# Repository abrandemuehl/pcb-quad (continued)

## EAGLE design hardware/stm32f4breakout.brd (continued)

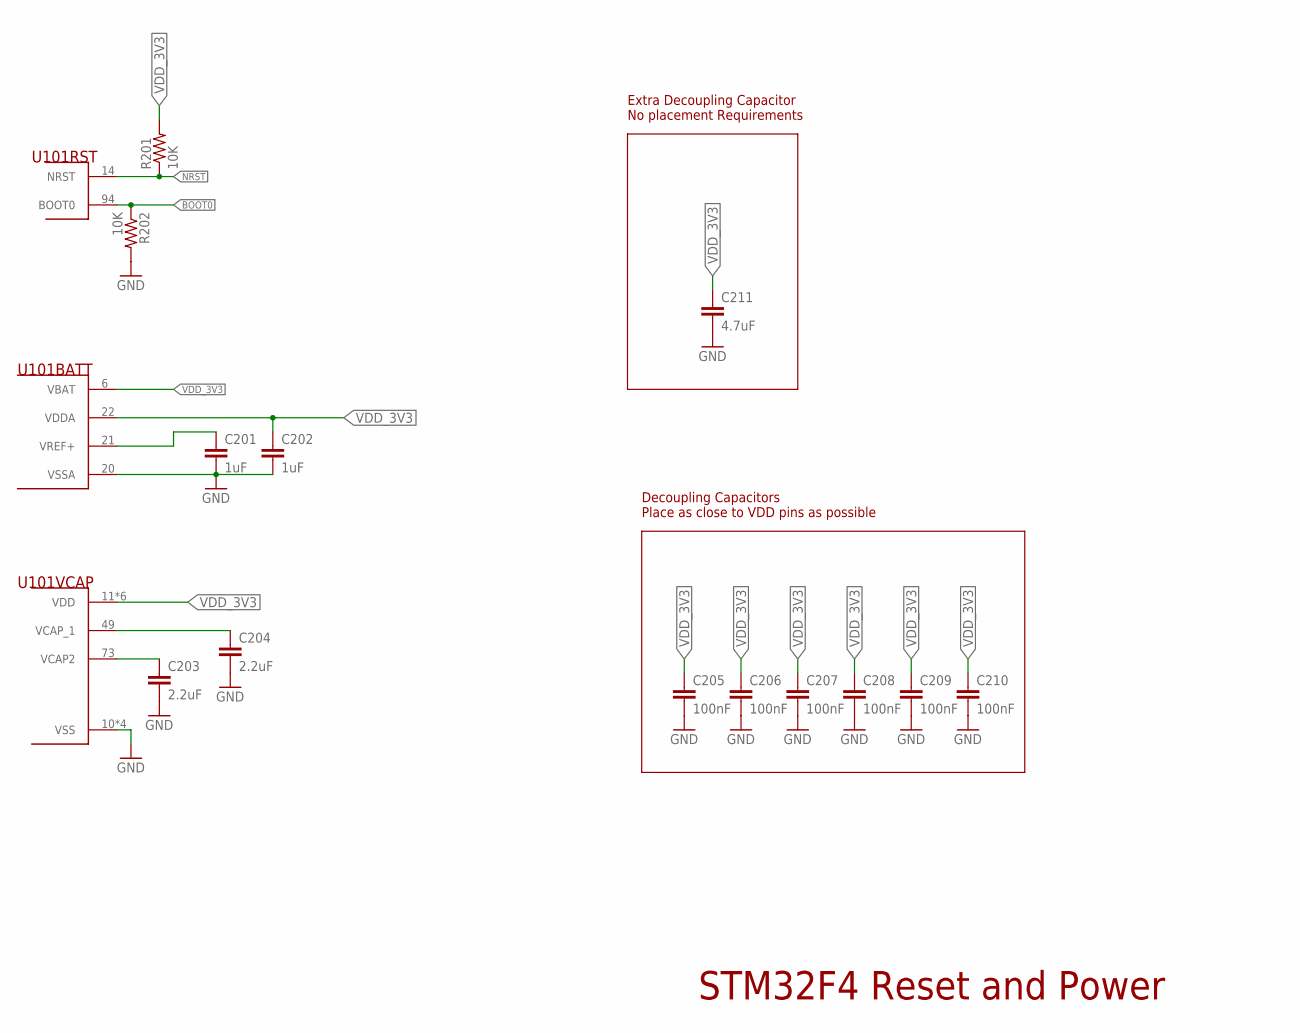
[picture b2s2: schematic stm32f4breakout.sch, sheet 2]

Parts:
C201, C202: 1uF; C0603
C203, C204: 2.2uF; C0603
C205, C206, C207, C208, C209, C210: 100nF; C0603
C211: 4.7uF; C0603
R201, R202: 10K; R0603
U101: STM32F427VGT6; LQFP-100

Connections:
BOOT0: R202.1, U101.94 (BOOT0); also elsewhere on the board
GND: C201.2, C202.2, C203.2, C204.2, C205.2, C206.2, C207.2, C208.2, C209.2, C210.2, C211.2, R202.2, U101.10 (VSS), U101.20 (VSSA), U101.27 (VSS), U101.74 (VSS), U101.99 (VSS); also elsewhere on the board
NRST: R201.1, U101.14 (NRST); also elsewhere on the board
VCAP2: C203.1, U101.73 (VCAP2)
VCAP_1: C204.1, U101.49 (VCAP_1)
VDD_3V3: C201.1, C202.1, C205.1, C206.1, C207.1, C208.1, C209.1, C210.1, C211.1, R201.2, U101.6 (VBAT), U101.11 (VDD), U101.19 (VDD), U101.21 (VREF+), U101.22 (VDDA), U101.28 (VDD), U101.50 (VDD), U101.75 (VDD), U101.100 (VDD); also elsewhere on the board

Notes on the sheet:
STM32F4 Reset and Power
Decoupling Capacitors Place as close to VDD pins as possible
Extra Decoupling Capacitor No placement Requirements

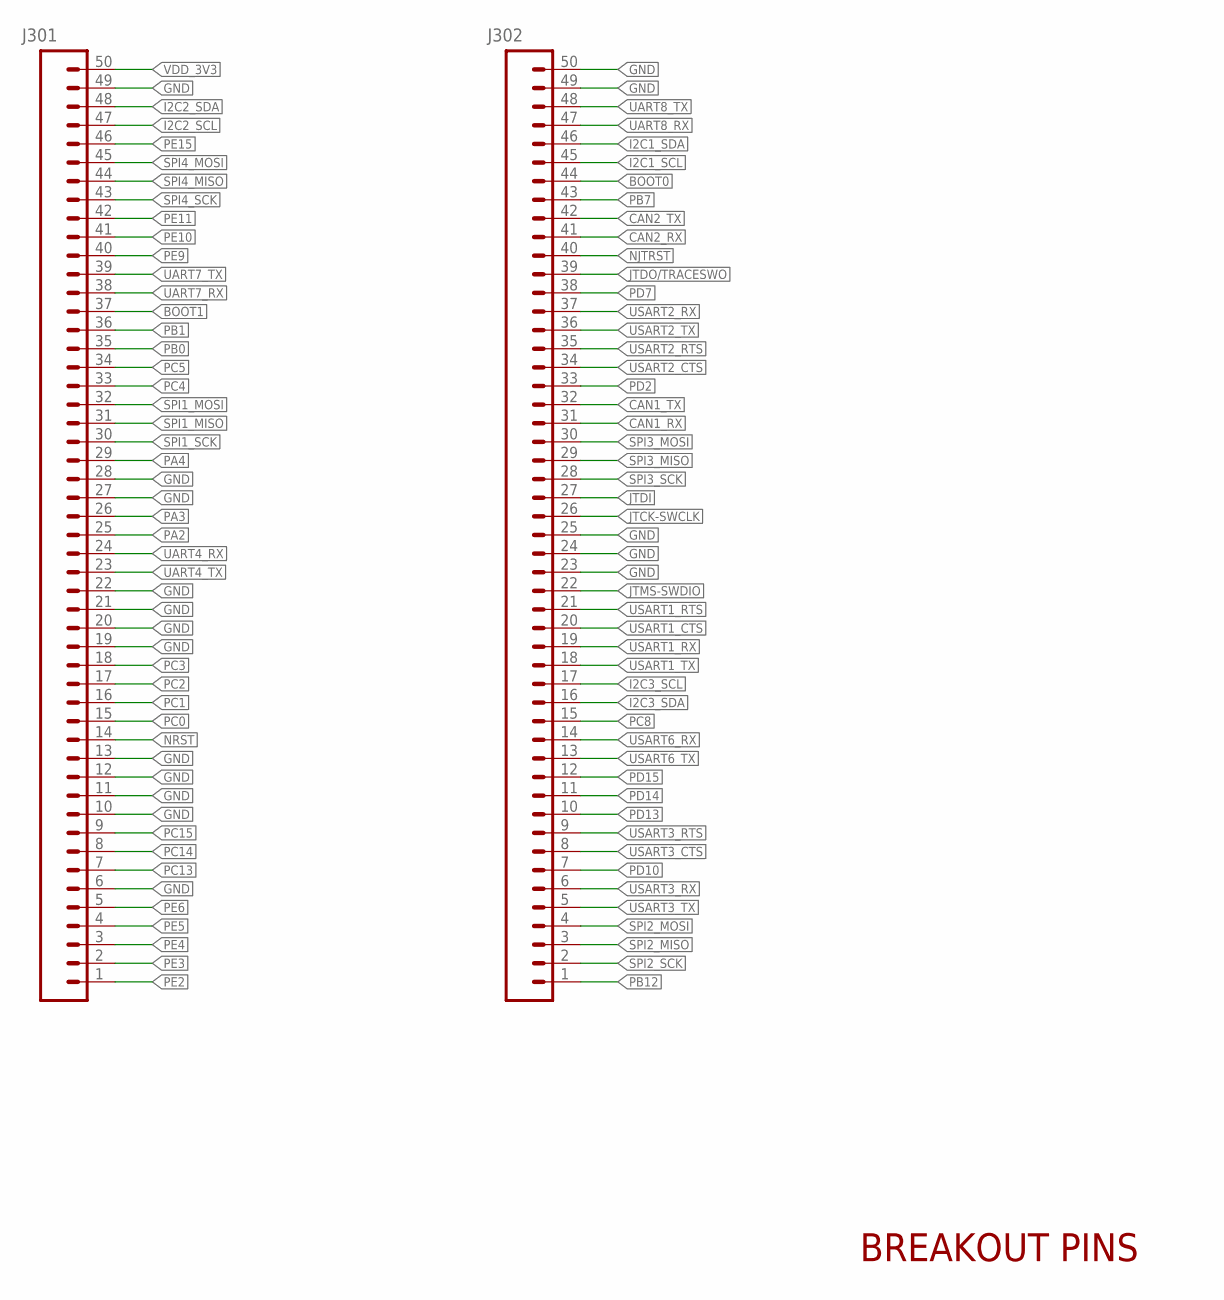
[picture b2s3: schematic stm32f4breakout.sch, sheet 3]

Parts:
J301, J302: PINHD-1X50; 1X50

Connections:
BOOT0: J302.44; also elsewhere on the board
BOOT1: J301.37; also elsewhere on the board
CAN1_RX: J302.31; also elsewhere on the board
CAN1_TX: J302.32; also elsewhere on the board
CAN2_RX: J302.41; also elsewhere on the board
CAN2_TX: J302.42; also elsewhere on the board
GND: J301.6, J301.10, J301.11, J301.12, J301.13, J301.19, J301.20, J301.21, J301.22, J301.27, J301.28, J301.49, J302.23, J302.24, J302.25, J302.49, J302.50; also elsewhere on the board
I2C1_SCL: J302.45; also elsewhere on the board
I2C1_SDA: J302.46; also elsewhere on the board
I2C2_SCL: J301.47; also elsewhere on the board
I2C2_SDA: J301.48; also elsewhere on the board
I2C3_SCL: J302.17; also elsewhere on the board
I2C3_SDA: J302.16; also elsewhere on the board
JTCK-SWCLK: J302.26; also elsewhere on the board
JTDI: J302.27; also elsewhere on the board
JTDO/TRACESWO: J302.39; also elsewhere on the board
JTMS-SWDIO: J302.22; also elsewhere on the board
NJTRST: J302.40; also elsewhere on the board
NRST: J301.14; also elsewhere on the board
PA2: J301.25; also elsewhere on the board
PA3: J301.26; also elsewhere on the board
PA4: J301.29; also elsewhere on the board
PB0: J301.35; also elsewhere on the board
PB1: J301.36; also elsewhere on the board
PB7: J302.43; also elsewhere on the board
PB12: J302.1; also elsewhere on the board
PC0: J301.15; also elsewhere on the board
PC1: J301.16; also elsewhere on the board
PC2: J301.17; also elsewhere on the board
PC3: J301.18; also elsewhere on the board
PC4: J301.33; also elsewhere on the board
PC5: J301.34; also elsewhere on the board
PC8: J302.15; also elsewhere on the board
PC13: J301.7; also elsewhere on the board
PC14: J301.8; also elsewhere on the board
PC15: J301.9; also elsewhere on the board
PD2: J302.33; also elsewhere on the board
PD7: J302.38; also elsewhere on the board
PD10: J302.7; also elsewhere on the board
PD13: J302.10; also elsewhere on the board
PD14: J302.11; also elsewhere on the board
PD15: J302.12; also elsewhere on the board
PE2: J301.1; also elsewhere on the board
PE3: J301.2; also elsewhere on the board
PE4: J301.3; also elsewhere on the board
PE5: J301.4; also elsewhere on the board
PE6: J301.5; also elsewhere on the board
PE9: J301.40; also elsewhere on the board
PE10: J301.41; also elsewhere on the board
PE11: J301.42; also elsewhere on the board
PE15: J301.46; also elsewhere on the board
SPI1_MISO: J301.31; also elsewhere on the board
SPI1_MOSI: J301.32; also elsewhere on the board
SPI1_SCK: J301.30; also elsewhere on the board
SPI2_MISO: J302.3; also elsewhere on the board
SPI2_MOSI: J302.4; also elsewhere on the board
SPI2_SCK: J302.2; also elsewhere on the board
SPI3_MISO: J302.29; also elsewhere on the board
SPI3_MOSI: J302.30; also elsewhere on the board
SPI3_SCK: J302.28; also elsewhere on the board
SPI4_MISO: J301.44; also elsewhere on the board
SPI4_MOSI: J301.45; also elsewhere on the board
SPI4_SCK: J301.43; also elsewhere on the board
UART4_RX: J301.24; also elsewhere on the board
UART4_TX: J301.23; also elsewhere on the board
UART7_RX: J301.38; also elsewhere on the board
UART7_TX: J301.39; also elsewhere on the board
UART8_RX: J302.47; also elsewhere on the board
UART8_TX: J302.48; also elsewhere on the board
USART1_CTS: J302.20; also elsewhere on the board
USART1_RTS: J302.21; also elsewhere on the board
USART1_RX: J302.19; also elsewhere on the board
USART1_TX: J302.18; also elsewhere on the board
USART2_CTS: J302.34; also elsewhere on the board
USART2_RTS: J302.35; also elsewhere on the board
USART2_RX: J302.37; also elsewhere on the board
USART2_TX: J302.36; also elsewhere on the board
USART3_CTS: J302.8; also elsewhere on the board
USART3_RTS: J302.9; also elsewhere on the board
USART3_RX: J302.6; also elsewhere on the board
USART3_TX: J302.5; also elsewhere on the board
USART6_RX: J302.14; also elsewhere on the board
USART6_TX: J302.13; also elsewhere on the board
VDD_3V3: J301.50; also elsewhere on the board

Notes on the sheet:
BREAKOUT PINS

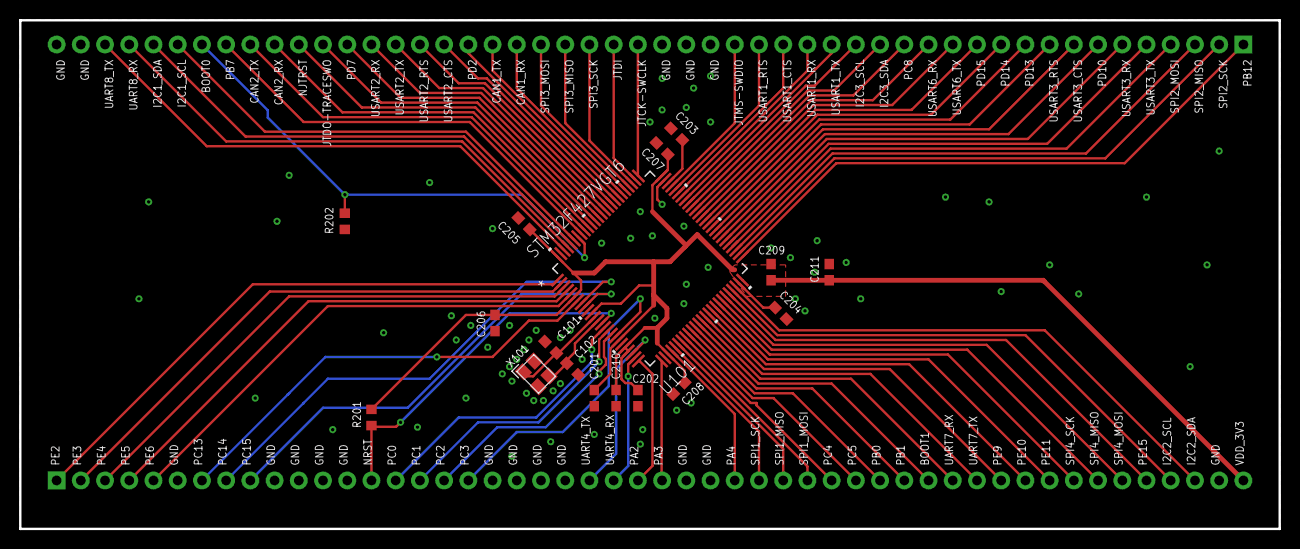
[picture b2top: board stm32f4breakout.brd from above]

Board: 2 copper layers, 132.1 x 53.3 mm, 19 parts (0 on the bottom side), 88 nets.

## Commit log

2017-09-11 Add oscillator library part
2017-09-15 Continue work on schematic
2017-09-18 Create breakout board for STM32F4
2017-09-18 Add 4.7uF decoupling cap
2017-09-18 Add breakout schematic pdf
2017-09-19 Fix final airwires on breakout, add DRC file
2017-09-22 Add USB-UART, BNO055
2017-09-25 Wire BNO055, Added XBEE
2017-09-26 Add power connectors, finish BNO055
2017-09-29 Finish library cleanup
2017-09-29 First draft schematic done
2017-09-29 Fixes and start layout
2017-10-02 Add board outline and make some placements
2017-10-03 Passing DRC on the layout
2017-10-13 Add flash loader
2017-10-13 Redo board power layout
2017-10-21 Minor changes
2017-10-21 First software commit
2017-10-23 Every interrupt vector MUST have LSB set to 0
    This is required by the ARM cortex architecture to indicate that the
    code is thumb code
2017-10-23 Use correct ldscript
2017-10-23 Build and run C++ code
2017-10-24 Set PLL frequency to match board
2017-10-24 Fix HSE_VALUE to match our crystal
2017-10-31 Working uart
2017-11-03 Set HSE oscillator value
2017-11-03 Convert line endings
2017-11-06 Working I2C
2017-11-10 Fix up I2C bugs, initial working bno055
2017-11-13 Not working, but progress
2017-11-15 Working PWM Timer
    Added standard peripheral drivers for timer support, created function for PWM control on TIM3
2017-11-27 Configure TIM2 to 1 MHz
2017-11-27 Add periodic timer commands, sleep commands, reformat
2017-11-27 Use sleep commands
2017-11-27 Try to sample the bno again
2017-11-28 Make BNO055 use external crystal.
    As of this commit, the bno055 outputs very good fused data.
2017-11-28 Start pid
2017-12-01 Add calibration for IMU
2017-12-04 Remove unneeded sleeps
2017-12-04 Remove kalman stuff
2017-12-05 Replace loader script, can flash board but no responses
2017-12-10 Changed PWM frequency and lower/upper bounds
    Changed PWM frequency from 500Hz to 100Hz and set the lower bound of the motor control to 1ms and the upper bound to 2ms
2017-12-11 Set right motors
2018-02-04 Final code commit
2018-02-04 Add readme
